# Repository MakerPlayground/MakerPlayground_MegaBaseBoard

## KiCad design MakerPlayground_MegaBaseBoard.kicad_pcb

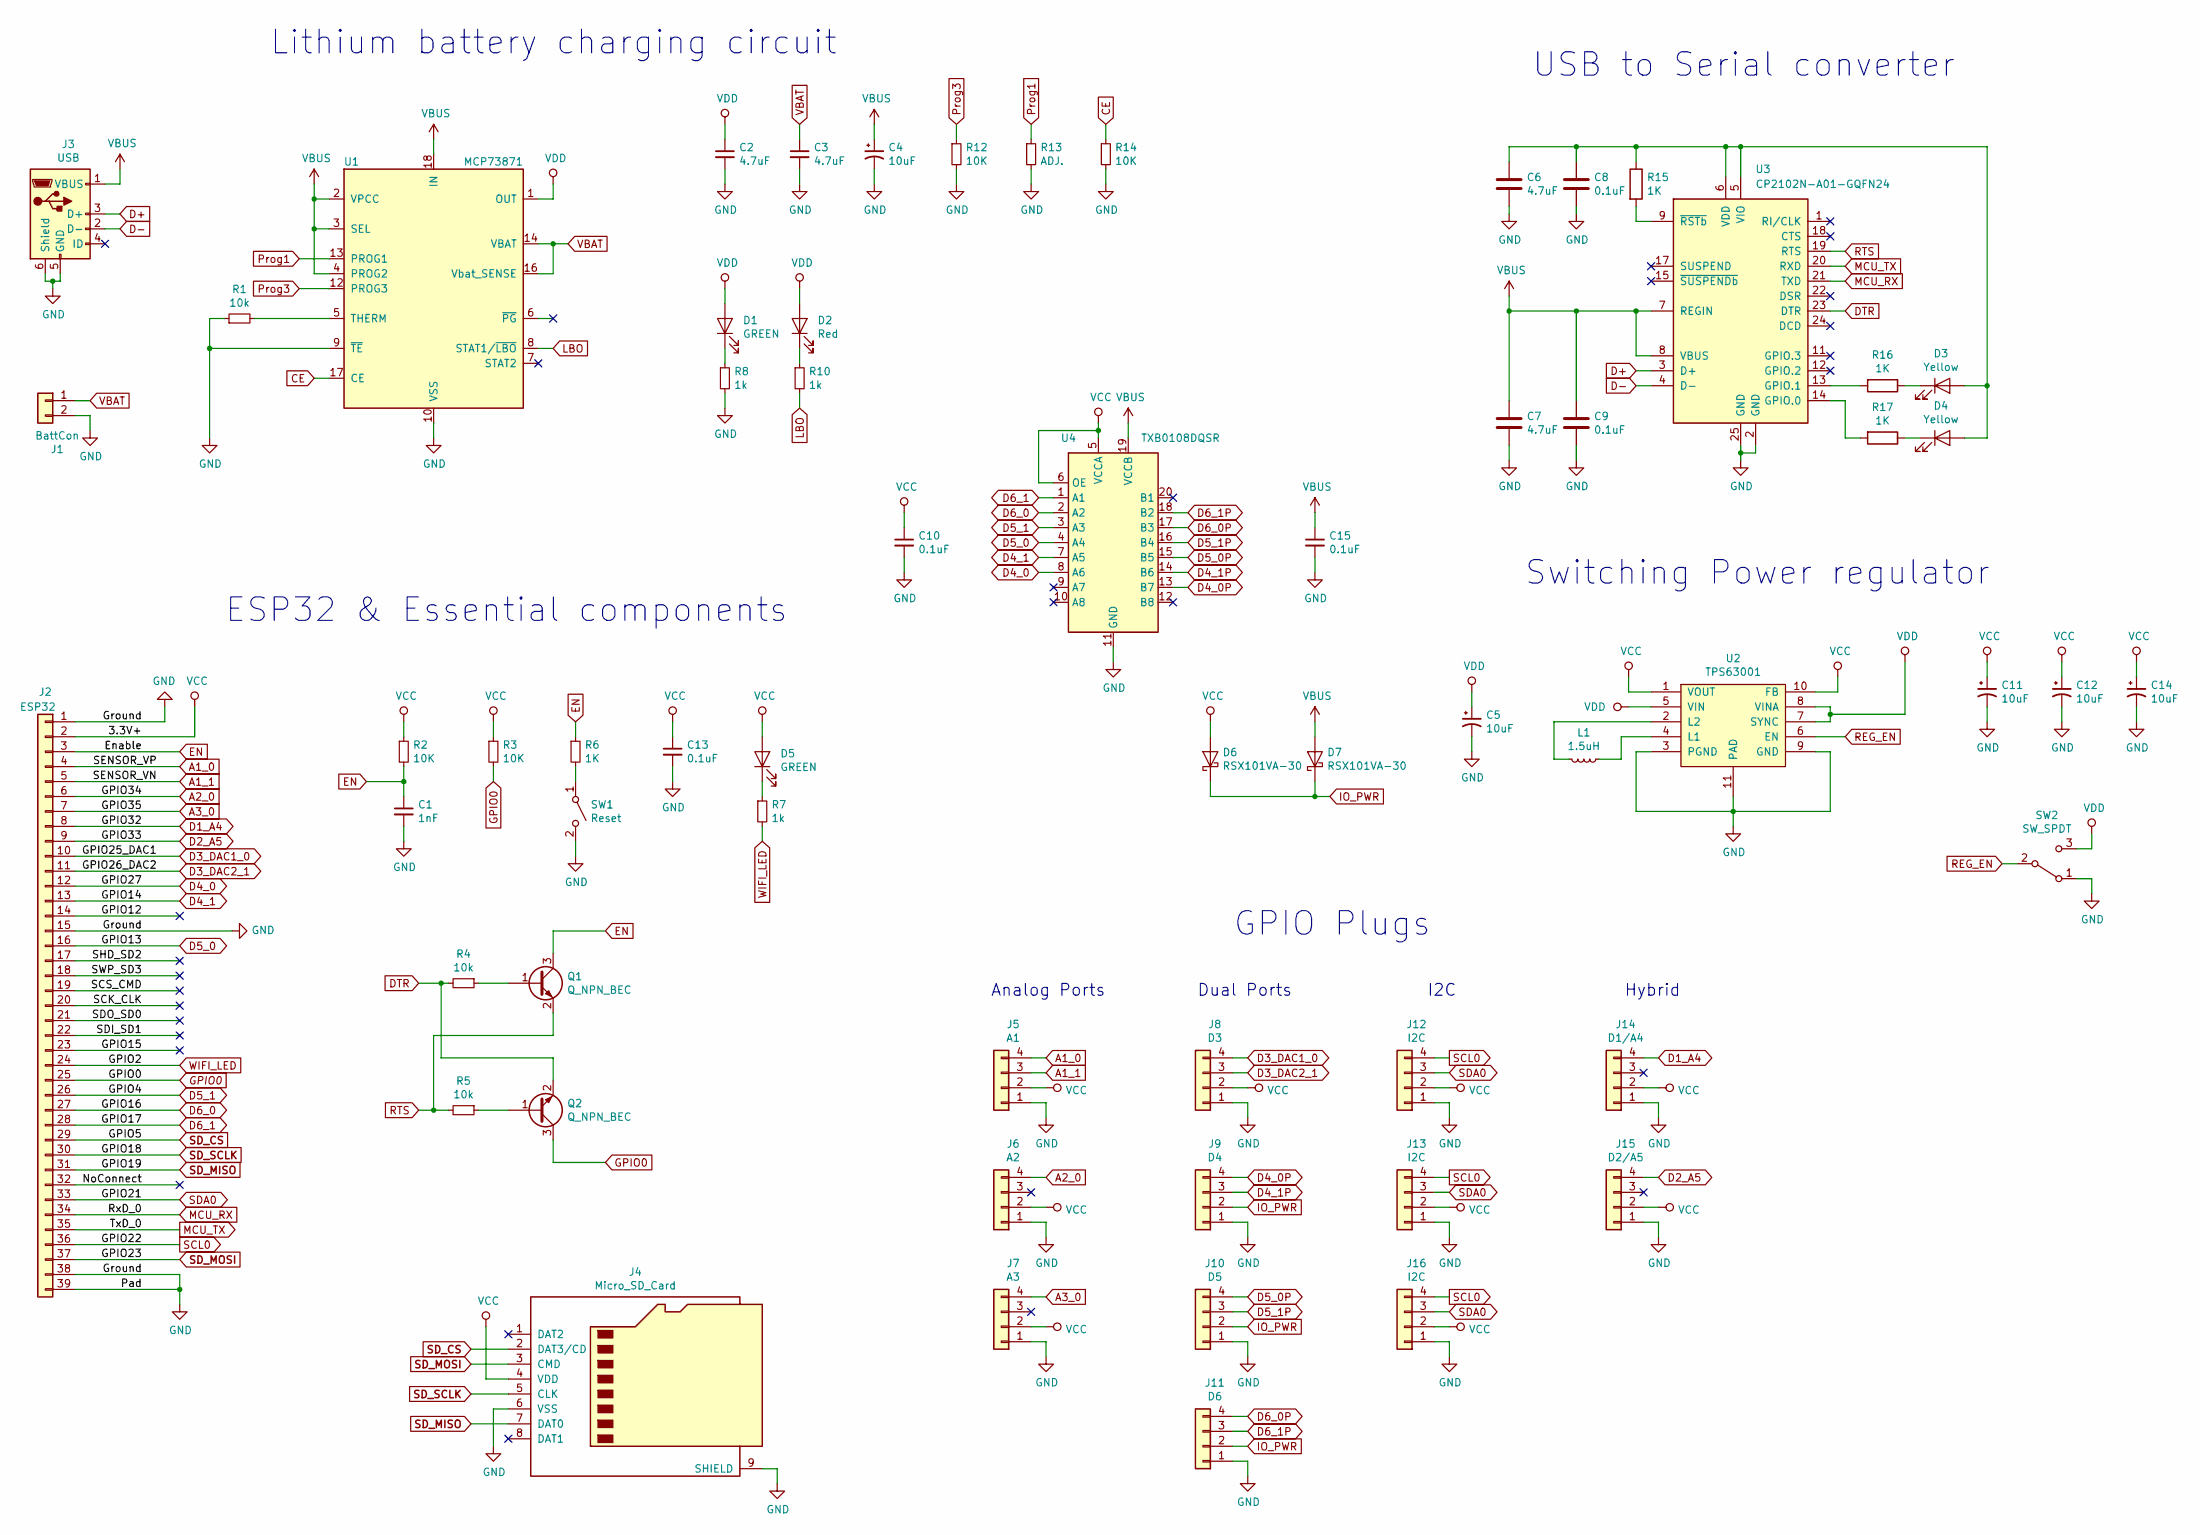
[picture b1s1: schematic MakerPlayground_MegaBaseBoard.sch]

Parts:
C1: 1nF; C_0603_1608Metric
C2, C3, C6, C7: 4.7uF; C_0603_1608Metric
C4, C5, C11, C12, C14: 10uF; C_0805_2012Metric
C8, C9, C10, C13, C15: 0.1uF; C_0603_1608Metric
D1, D5: GREEN; LED_0603_1608Metric
D2: Red; LED_0603_1608Metric
D3, D4: Yellow; LED_0603_1608Metric
D6, D7: RSX101VA-30; D_TUMD2
J1: BattCon; JST_PH_S2B-PH-K_1x02_P2.00mm_Horizontal
J2: ESP32; ESP32-WROOM-32
J3: USB; USB_Micro-B_Amphenol_10118193_Horizontal
J4: Micro_SD_Card; GTK_TFMS08TK-PP-02; Mfg Part No. TFMS08TK-PP-02
J5: A1; JST_PH_B4B-PH-K_1x04_P2.00mm_Vertical
J6: A2; JST_PH_B4B-PH-K_1x04_P2.00mm_Vertical
J7: A3; JST_PH_B4B-PH-K_1x04_P2.00mm_Vertical
J8: D3; JST_PH_B4B-PH-K_1x04_P2.00mm_Vertical
J9: D4; JST_PH_B4B-PH-K_1x04_P2.00mm_Vertical
J10: D5; JST_PH_B4B-PH-K_1x04_P2.00mm_Vertical
J11: D6; JST_PH_B4B-PH-K_1x04_P2.00mm_Vertical
J12, J13, J16: I2C; JST_PH_B4B-PH-K_1x04_P2.00mm_Vertical
J14: D1/A4; JST_PH_B4B-PH-K_1x04_P2.00mm_Vertical
J15: D2/A5; JST_PH_B4B-PH-K_1x04_P2.00mm_Vertical
L1: 1.5uH; L_1008(2520); Mouser Part No. 81-DFE201610P-2R2MP2
Q1, Q2: Q_NPN_BEC; SOT-23
R1, R4, R5: 10k; R_0603_1608Metric
R2, R3, R12, R14: 10K; R_0603_1608Metric
R6, R15, R16, R17: 1K; R_0603_1608Metric
R7, R8, R10: 1k; R_0603_1608Metric
R13: ADJ.; R_0603_1608Metric
SW1: Reset; TTS-35-C-1-P
SW2: SW_SPDT; SW_SPDT_CK-JS102011JCQN
U1: MCP73871; QFN-20-1EP_4x4mm_P0.5mm_EP2.5x2.5mm
U2: TPS63001; VSON-10-1EP_3x3mm_P0.5mm_EP1.65x2.4mm_ThermalVias
U3: CP2102N-A01-GQFN24; QFN-24-1EP_4x4mm_P0.5mm_EP2.6x2.6mm
U4: TXB0108DQSR; USON-20_2x4mm_P0.4mm

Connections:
/GPIO12: J2.14
/GPIO15: J2.23
/NoConnect: J2.32
/SCK_CLK: J2.20
/SCS_CMD: J2.19
/SDI_SD1: J2.22
/SDO_SD0: J2.21
/SHD_SD2: J2.17
/SWP_SD3: J2.18
A1_0: J2.4, J5.4
A1_1: J2.5, J5.3
A2_0: J2.6, J6.4
A3_0: J2.7, J7.4
CE: R14.1, U1.17 (CE)
D1_A4: J2.8, J14.4
D2_A5: J2.9, J15.4
D3_DAC1_0: J2.10, J8.4
D3_DAC2_1: J2.11, J8.3
D4_0: J2.12, U4.8 (A6)
D4_0P: J9.4, U4.13 (B7)
D4_1: J2.13, U4.7 (A5)
D4_1P: J9.3, U4.14 (B6)
D5_0: J2.16, U4.4 (A4)
D5_0P: J10.4, U4.15 (B5)
D5_1: J2.26, U4.3 (A3)
D5_1P: J10.3, U4.16 (B4)
D6_0: J2.27, U4.2 (A2)
D6_0P: J11.4, U4.17 (B3)
D6_1: J2.28, U4.1 (A1)
D6_1P: J11.3, U4.18 (B2)
D+: J3.3 (D+), U3.3 (D+)
D-: J3.2 (D-), U3.4 (D-)
DTR: Q2.2 (E), R4.2, U3.23 (DTR)
EN: C1.1, J2.3, Q1.3 (C), R2.2, R6.1
GND: C1.2, C2.2, C3.2, C4.2, C5.2, C6.2, C7.2, C8.2, C9.2, C10.2, C11.2, C12.2, C13.2, C14.2, C15.2, J1.2, J2.1, J2.15, J2.38, J2.39, J3.5 (GND), J3.6 (Shield), J4.6 (VSS), J4.9 (SHIELD), J5.1, J6.1, J7.1, J8.1, J9.1, J10.1, J11.1, J12.1, J13.1, J14.1, J15.1, J16.1, R1.1, R8.2, R12.2, R13.2, R14.2, SW1.2 (B), SW2.1 (A), U1.9 (~TE), U1.10 (VSS), U1.11 (VSS), U1.21 (VSS), U2.3 (PGND), U2.9 (GND), U2.11 (PAD), U3.2 (GND), U3.25 (GND), U4.11 (GND)
GPIO0: J2.25, Q2.3 (C), R3.2
IO_PWR: D6.1 (K), D7.1 (K), J9.2, J10.2, J11.2
LBO: R10.2, U1.8 (STAT1/~LBO~)
MCU_RX: J2.34, U3.21 (TXD)
MCU_TX: J2.35, U3.20 (RXD)
unnamed: C6.1, C8.1, D3.2 (A), D4.2 (A), R15.1, U3.5 (VIO), U3.6 (VDD)
unnamed: D1.1 (K), R8.1
unnamed: D2.1 (K), R10.1
unnamed: D3.1 (K), R16.1
unnamed: D4.1 (K), R17.1
unnamed: D5.1 (K), R7.1
unnamed: L1.1, U2.4 (L1)
unnamed: L1.2, U2.2 (L2)
unnamed: Q1.1 (B), R4.1
unnamed: Q2.1 (B), R5.1
unnamed: R1.2, U1.5 (THERM)
unnamed: R6.2, SW1.1 (A)
unnamed: R15.2, U3.9 (~RSTb)
unnamed: R16.2, U3.13 (GPIO.1)
unnamed: R17.2, U3.14 (GPIO.0)
Prog1: R13.1, U1.13 (PROG1)
Prog3: R12.1, U1.12 (PROG3)
REG_EN: SW2.2 (B), U2.6 (EN)
RTS: Q1.2 (E), R5.2, U3.19 (RTS)
SCL0: J2.36, J12.4, J13.4, J16.4
SDA0: J2.33, J12.3, J13.3, J16.3
SD_CS: J2.29, J4.2 (DAT3/CD)
SD_MISO: J2.31, J4.7 (DAT0)
SD_MOSI: J2.37, J4.3 (CMD)
SD_SCLK: J2.30, J4.5 (CLK)
VBAT: C3.1, J1.1, U1.14 (VBAT), U1.15 (VBAT), U1.16 (Vbat_SENSE)
VBUS: C4.1, C7.1, C9.1, C15.1, D7.2 (A), J3.1 (VBUS), U1.2 (VPCC), U1.3 (SEL), U1.4 (PROG2), U1.18 (IN), U1.19 (IN), U3.7 (REGIN), U3.8 (VBUS), U4.19 (VCCB)
VCC: C10.1, C11.1, C12.1, C13.1, C14.1, D5.2 (A), D6.2 (A), J2.2, J4.4 (VDD), J5.2, J6.2, J7.2, J8.2, J12.2, J13.2, J14.2, J15.2, J16.2, R2.1, R3.1, U2.1 (VOUT), U2.10 (FB), U4.5 (VCCA), U4.6 (OE)
VDD: C2.1, C5.1, D1.2 (A), D2.2 (A), SW2.3 (C), U1.1 (OUT), U1.20 (OUT), U2.5 (VIN), U2.7 (SYNC), U2.8 (VINA)
WIFI_LED: J2.24, R7.2

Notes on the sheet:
Lithium battery charging circuit
USB to Serial converter
Switching Power regulator
ESP32 & Essential components
GPIO Plugs
Analog Ports
Dual Ports
I2C
Hybrid

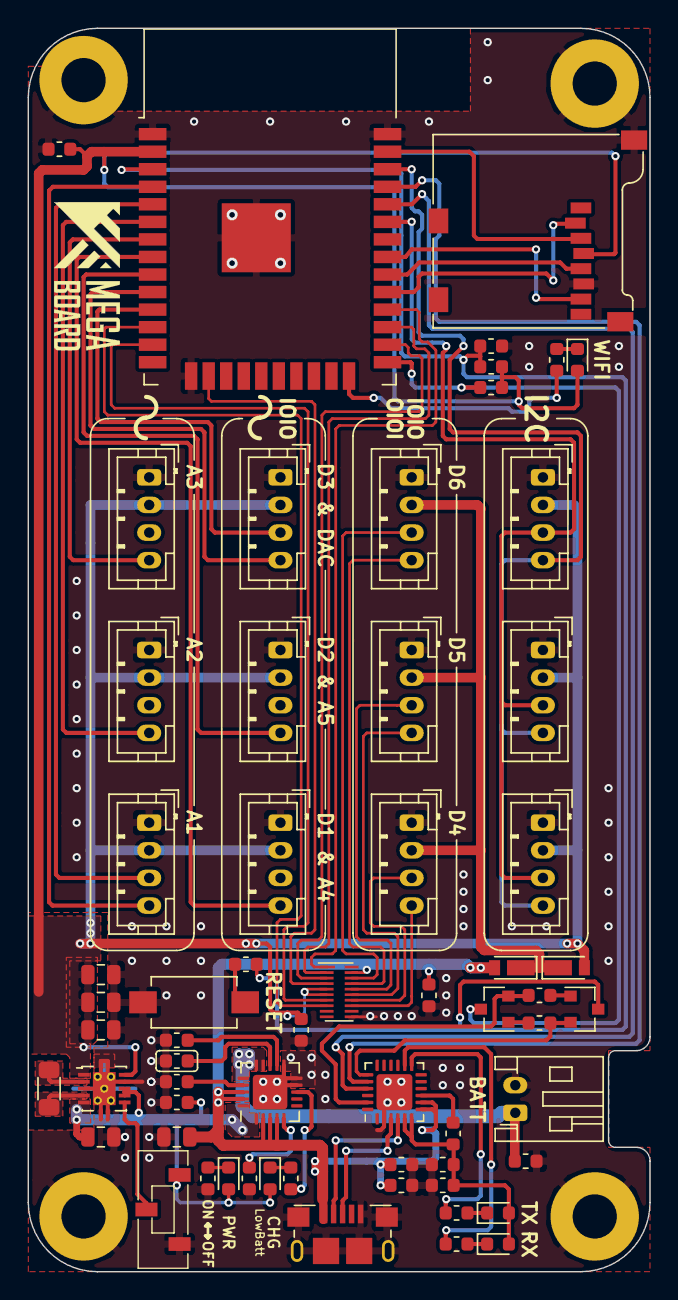
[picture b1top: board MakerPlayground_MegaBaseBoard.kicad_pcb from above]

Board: 2 copper layers, 45.0 x 90.0 mm, 62 parts (0 on the bottom side), 61 nets.

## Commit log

2018-11-04 The first commit of MakerPlayground_MegaBaseBoard.
2018-11-07 Add ON/OFF switch & new alignment for PWR/CHG LED.
